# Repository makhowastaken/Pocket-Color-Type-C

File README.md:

# Pocket/Color Type-C
A simple USB Type-C mod to replace the OEM DC jack on Game Boy Pockets, Game Boy Colors, and anything inbetween. 

**THIS TESTED AND WORKING**

This repo includes the board files for the USB Type-C power port, cut jigs for some console shells, and some other misc PoCo mod files. Installing a [GBPP](https://github.com/marshallh/gbpp) but don't want to use the OEM DC jack for charging? This is the right place!

Also, I didn't proofread this shit at all so expect typos. I may or may not fix them especially since it took me four years to actually make this documentation. 

---

## Type-C Board

Very heavily inspired by [giltesa's Game Boy Pocket USB-C Charging Kit.](https://github.com/giltesa/Game-Boy-Pocket-USB-C-charging-kit) I did recreate his charge board from scratch but credit where credit is due. 

[Lowpolysaurus](https://lowpoly.dk/) was kind enough to let me use his pics for my mod since I don't actually have a completed one. Please be sure to give him a follow on his various socials ;)

The original board (giltesa's) is sold in 1.0mm variants but if you order my board, you may only have 0.8mm and 1.6mm options. I'd recommend 0.8mm if you cannot get 1.0mm. 

OSHPARK shared project: [https://oshpark.com/shared_projects/eB7KeXwI](https://oshpark.com/shared_projects/eB7KeXwI)

Uses this six pin USB Type-C port: [https://www.aliexpress.com/item/32885941456.html](https://www.aliexpress.com/item/32885941456.html)

And requires two 5.1k 0603 resistors to be installed if you want the port to be able to negotiate 5v from a USB Type-C host. This is optional but the device will not be able to negotiate 5v when connected to a USB Type-C host but will still charge when connected to a USB Type-A host. 

The instructions in giltesa's repo linked above will be identical for this board too and I'd recommend giving them a gander. The only part you need to actually remove for this board, however, is the OEM DC jack. You may leave the remainder of the circuit in-place though you may need to lift the DC jack fuse (why not slide it off one of the pads and just reuse it?) to connect the port to the charge circuit of your battery mod rather than the main voltage rail of the Game Boy. 

Otherwise, here are steps to install: 

* Order the board in 0.8mm thickness from the OSHPARK shared link above (or download the gerbers from this repo and get 1.0mm elsewhere). 1.6mm may work but none of the cut jigs will be aligned. 
* Remove the original DC jack on the Pocket and remove any excess solder from the holes with a wick or solder sucker.
* Install the Type-C port on the board. The resistors should be installed later. 
* Place the assembly on the Pocket board and ensure that the board is aligned so that the port is not wonky. The five pads on the bottom of the USB Type-C board should align with the five holes left over from the DC jack. 
* Tape the boards together temporarily so you may flip the Pocket over and solder to the bottom.
* Use a LOT of solder for one hole to tack the board down and remove the tape. You need to ensure that enough solder is in the hole to reach the board on the other side and wet to the pads. 
* Remove the tape to ensure you have a solid joint. Repeat steps if the board comes off with the tape. 
* Optional step, you may add component legs (e.g. trimmed off a THT LED or resistor or the like) to three of the five pads for additional structural support as solder alone may fail over time. Otherwise, the holes can be used as an indicator that solder has been wet to both boards. 
* Solder the other four pads to the holes. 
* Now you can install the resistors. The four pads are directly behind the USB Type-C port and one of them overlaps with one of the mounting pads for the board. 
* Ground is connected through the board, 5v may be tapped either from the on-board fuse or you may pull from the biggest pad in the middle. 

Ensure the port is aligned properly before using the cut jig to cut a hole in your shell! Also, do not forget to trim the OEM DC jack supports from the housing too as the wider USB Type-C port will not fit between them. 

---

## Cut Jigs

If you're installing this board in an OEM-like shell, my cut jigs may be useful for you. Both are designed with the respective GilTesa mods in mind which use 1.0mm PCBs. If you ordered my boards in a different thickness, keep this spacing in mind. The next closest common thickness (e.g. what OshPark can make) will be 0.8mm which should be *close enough* to work without much adjustment. Measure twice, cut once and all that. 

Pocket Shell Jig: https://www.printables.com/model/141352-game-boy-pocket-usb-type-c-port-cut-jig

Color Shell Jig: https://www.printables.com/model/281959-game-boy-color-usb-type-c-port-cut-jig

STLs may be downloaded from either this repo or the printables links above. They are the same files and only hosted here as well for convenience. 

---

## PoCo Extras

Also here for convenience and because I really don't think they need their own repo. Both of these parts will only really work for chop method PoCo builds. 

If you have a full custom PCB (e.g. [Skimzor's SZ-POCO,](https://github.com/skimzor/SZ-POCO) [N64-Freak's Pocket-Color,](https://github.com/N64-Freak/GB-Mods/tree/main/Pocket-Color) [NatalieTheNerd's YAPoco,](https://github.com/nataliethenerd/YAPoco) or [BucketMouse's Game Boy Pocket Color](https://github.com/MouseBiteLabs/Game-Boy-Pocket-Color)), then you probably won't be using this. 

I have included a simple "IR Window". Print in clear or other IR transparent filament or it won't work. IR communication tested working with this on an original Game Boy Color and Analogue Pocket both. 

And I also included the push-button power bracket I am using. The bracket was designed for the 6mm wide button I found in my junk drawer (sorry, that means no part number) and I glued the button to the bracket. The bracket itself is press fit into the shell. The circuit powering this... power switch is the main board from my [soft-latching power button project.](https://github.com/makhowastaken/Soft-Latching-Power-Button)

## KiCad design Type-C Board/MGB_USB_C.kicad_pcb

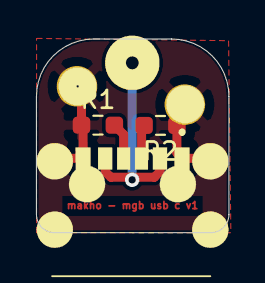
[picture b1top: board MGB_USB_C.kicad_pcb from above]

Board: 2 copper layers, 10.7 x 10.8 mm, 4 parts (0 on the bottom side), 4 nets.

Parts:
J1: Conn_01x05_Male; mgb_power_pad_refs
P1: USB_C_Plug_USB2.0; TYPEC31M17
R1, R2: 5.1k; R_0603_1608Metric_Pad0.98x0.95mm_HandSolder

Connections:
GND: J1.2, J1.3, J1.4, J1.5, P1.A12, P1.B12, P1.MH1, P1.MH2, P1.MH3, P1.MH4, R1.1, R2.1
unnamed: J1.1, P1.A9, P1.B9
unnamed: P1.A5, R1.2
unnamed: P1.B5, R2.2
